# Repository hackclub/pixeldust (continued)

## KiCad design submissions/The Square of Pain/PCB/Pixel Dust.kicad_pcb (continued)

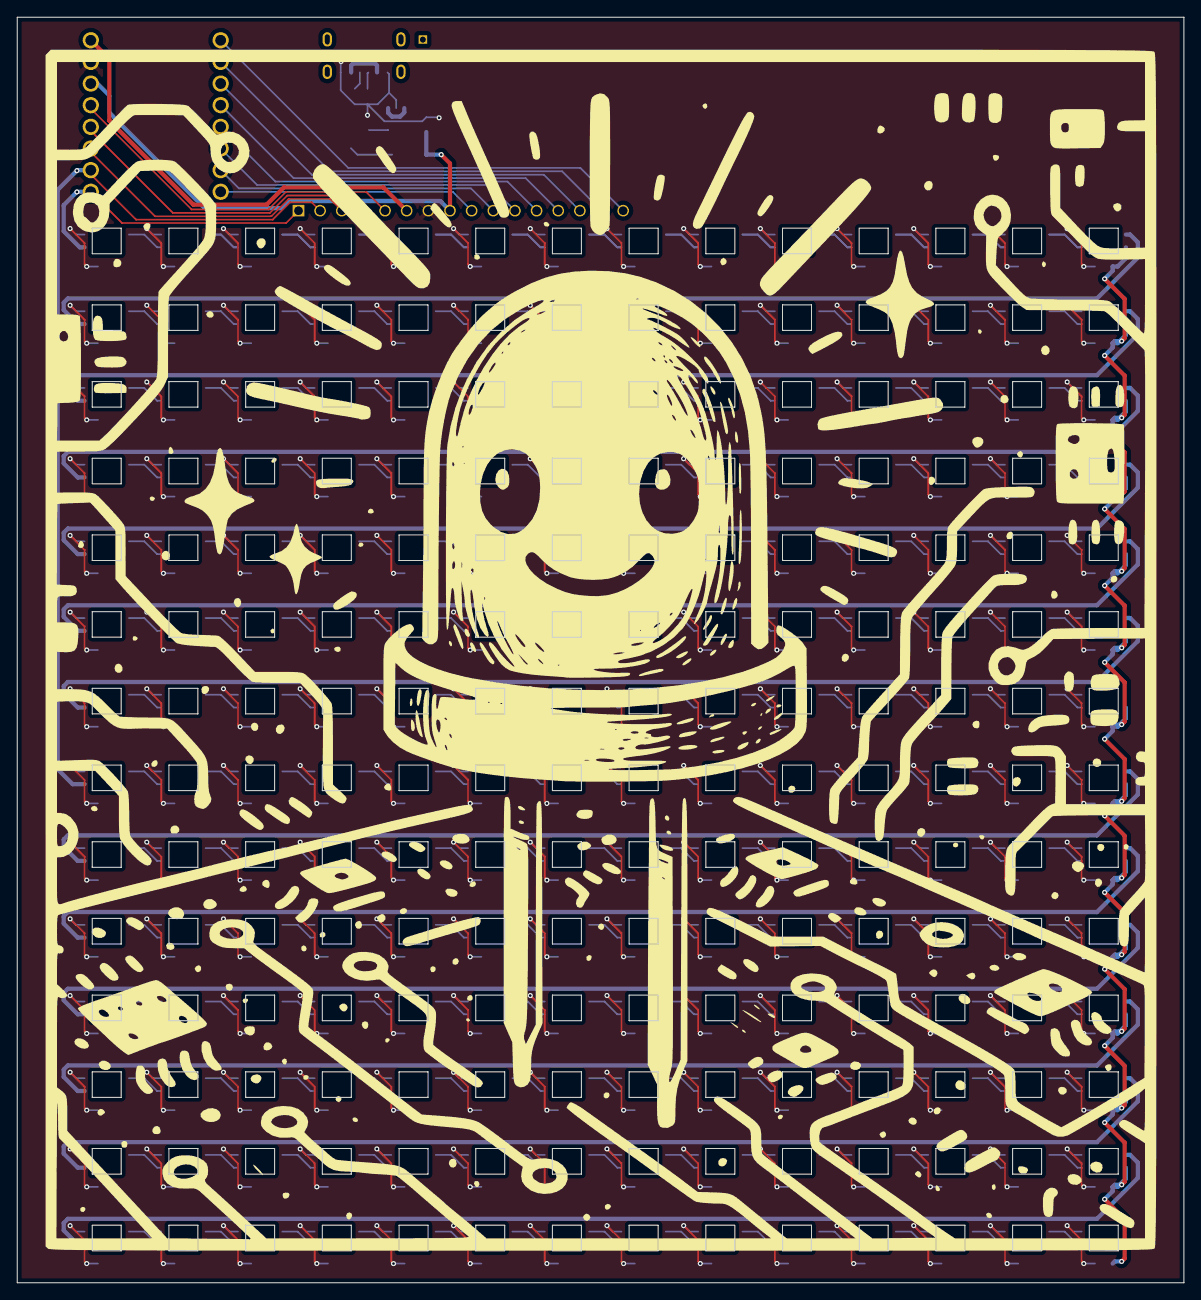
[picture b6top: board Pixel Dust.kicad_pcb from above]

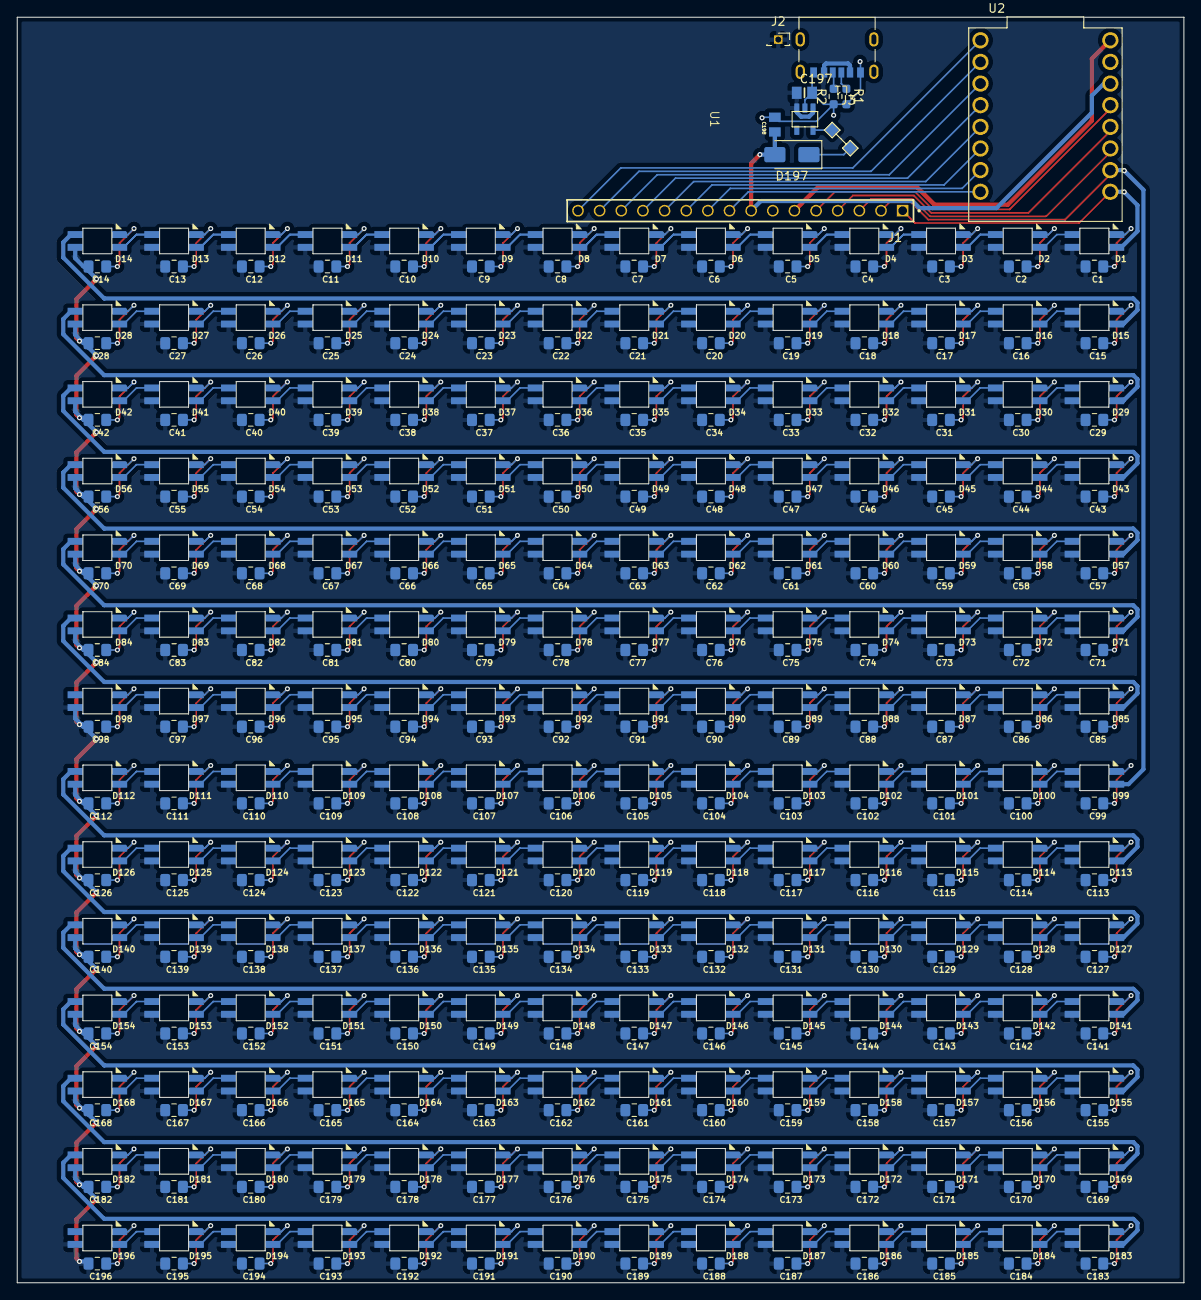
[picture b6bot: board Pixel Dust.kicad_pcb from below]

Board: 2 copper layers, 136.9 x 148.5 mm, 403 parts (403 on the bottom side), 215 nets.
